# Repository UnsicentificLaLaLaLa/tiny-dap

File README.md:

# tiny-dap

[TOC]

## 介绍

基于 TinyUSB 和 CMSIS-5 实现的 CMSIS-DAP，支持 SWD 调试接口和串口通信。

选择 TinyUSB 作为协议栈的原因是 TinyUSB 开源免费，且适配多家 MCU，具有良好的通用性。

基于 CMSIS-5 实现 CMSIS-DAP 可以降低移植 DapLink 的难度，降低实现门槛。

## 文件结构

- hardware

    - v1.x

        tiny-dap 的硬件实现，使用 KiCad 7.0 设计，已生成生产文件和原理图。

        - production

            使用 KiCad 嘉立创提供的插件生成的生产文件。

- software

    tiny-dap 的软件实现，基于 MM32F0162D4Q。

## 适配芯片

目前计划采用 MM32F0162D4Q 作为 tiny-dap 的 MCU，后续也将计划在更多 QFN32 芯片上实现 tiny-dap，如果有精力的话。

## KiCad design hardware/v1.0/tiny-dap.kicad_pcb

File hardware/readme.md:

- v1.0
    - 初版 tiny-dap 硬件，基于 MM32F0162D4Q 设计
- v1.1
    - 基于 v1.0，移除了复位电路，移除了一个 LED，移除了微控制器电源的电容，移除了 USB 信号线上串联的 22R 电阻，减小了 PCB 尺寸

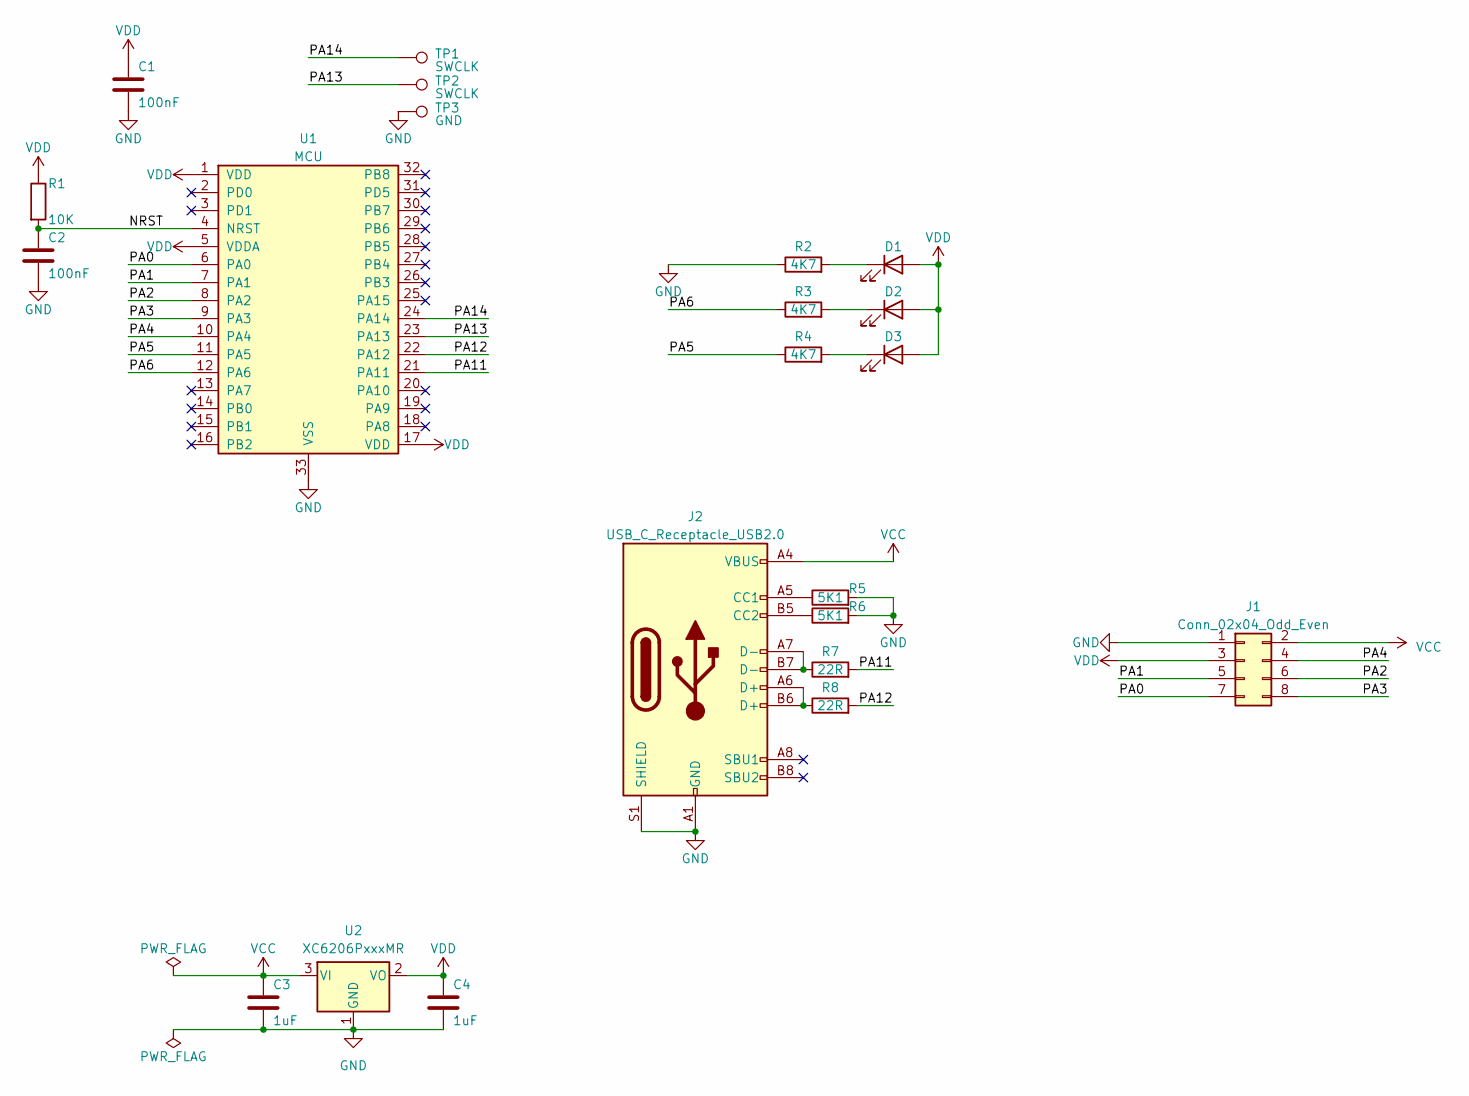
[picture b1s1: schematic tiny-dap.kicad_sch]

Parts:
C1, C2: 100nF; C_0603_1608Metric_Pad1.08x0.95mm_HandSolder
C3, C4: 1uF; C_0603_1608Metric_Pad1.08x0.95mm_HandSolder
D1, D2, D3: LED; LED_0603_1608Metric_Pad1.05x0.95mm_HandSolder
J1: Conn_02x04_Odd_Even; PinHeader_2x04_P2.54mm_Horizonal_Edge
J2: USB_C_Receptacle_USB2.0; USB_C_Receptacle_HRO_TYPE-C-31-M-12
R1: 10K; R_0603_1608Metric_Pad0.98x0.95mm_HandSolder
R2, R3, R4: 4K7; R_0603_1608Metric_Pad0.98x0.95mm_HandSolder
R5, R6: 5K1; R_0603_1608Metric_Pad0.98x0.95mm_HandSolder
R7, R8: 22R; R_0603_1608Metric_Pad0.98x0.95mm_HandSolder
TP1, TP2: SWCLK; TestPoint_Pad_D1.0mm
TP3: GND; TestPoint_Pad_D1.0mm
U1: MCU; QFN-32-1EP_5x5mm_P0.5mm_EP3.6x3.6mm
U2: XC6206PxxxMR; SOT-23

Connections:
/NRST: C2.1, R1.2, U1.4 (NRST)
/PA0: J1.7, U1.6 (PA0)
/PA1: J1.5, U1.7 (PA1)
/PA2: J1.6, U1.8 (PA2)
/PA3: J1.8, U1.9 (PA3)
/PA4: J1.4, U1.10 (PA4)
/PA5: R4.1, U1.11 (PA5)
/PA6: R3.1, U1.12 (PA6)
/PA11: R7.2, U1.21 (PA11)
/PA12: R8.2, U1.22 (PA12)
/PA13: TP2.1, U1.23 (PA13)
/PA14: TP1.1, U1.24 (PA14)
GND: C1.2, C2.2, C3.2, C4.2, J1.1, J2.A1 (GND), J2.A12 (GND), J2.B1 (GND), J2.B12 (GND), J2.S1 (SHIELD), R2.1, R5.2, R6.2, TP3.1, U1.33 (VSS), U2.1 (GND)
unnamed: D1.1 (K), R2.2
unnamed: D2.1 (K), R3.2
unnamed: D3.1 (K), R4.2
unnamed: J2.A5 (CC1), R5.1
unnamed: J2.B5 (CC2), R6.1
unnamed: J2.A6 (D+), J2.B6 (D+), R8.1
unnamed: J2.A7 (D-), J2.B7 (D-), R7.1
VCC: C3.1, J1.2, J2.A4 (VBUS), J2.A9 (VBUS), J2.B4 (VBUS), J2.B9 (VBUS), U2.3 (VI)
VDD: C1.1, C4.1, D1.2 (A), D2.2 (A), D3.2 (A), J1.3, R1.1, U1.1 (VDD), U1.5 (VDDA), U1.17 (VDD), U2.2 (VO)

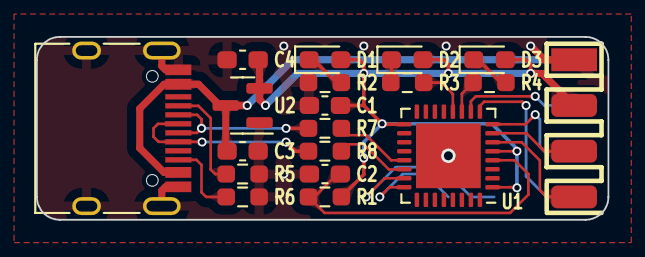
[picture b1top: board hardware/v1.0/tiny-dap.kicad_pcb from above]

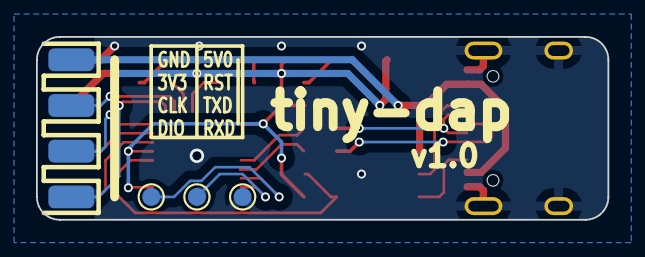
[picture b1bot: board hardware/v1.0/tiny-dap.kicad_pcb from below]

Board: 2 copper layers, 31.8 x 10.2 mm, 22 parts (3 on the bottom side), 22 nets.

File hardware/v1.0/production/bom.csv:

Designator,Footprint,Quantity,Value,LCSC Part #
"C1, C2",0603,2,100nF,
"C3, C4",0603,2,1uF,
"D1, D2, D3",0603,3,LED,
J1,PinHeader_2x04_P2.54mm_Horizonal_Edge,1,Conn_02x04_Odd_Even,
J2,USB_C_Receptacle_HRO_TYPE-C-31-M-12,1,USB_C_Receptacle_USB2.0,
R1,0603,1,10K,
"R2, R3, R4",0603,3,4K7,
"R5, R6",0603,2,5K1,
"R7, R8",0603,2,22R,
"TP1, TP2",TestPoint_Pad_D1.0mm,2,SWCLK,
TP3,TestPoint_Pad_D1.0mm,1,GND,
U1,QFN-32-1EP_5x5mm_P0.5mm_EP3.6x3.6mm,1,MCU,
U2,SOT-23,1,XC6206PxxxMR,

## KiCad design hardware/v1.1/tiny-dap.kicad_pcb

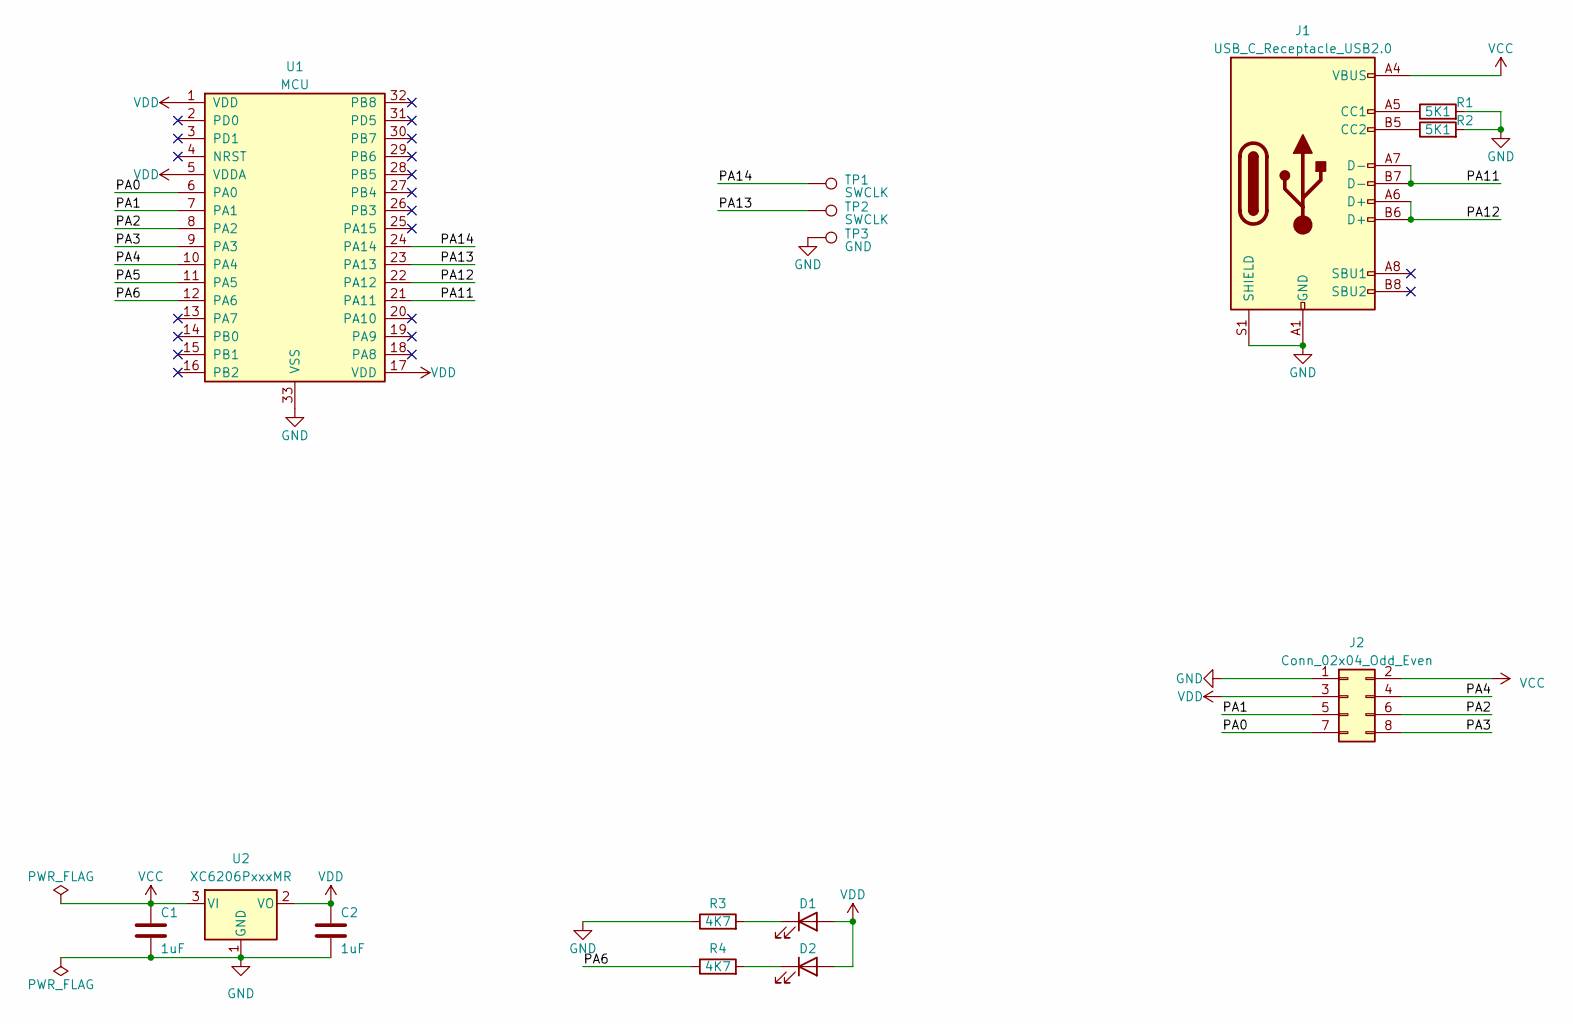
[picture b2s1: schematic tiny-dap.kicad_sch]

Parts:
C1, C2: 1uF; C_0603_1608Metric_Pad1.08x0.95mm_HandSolder
D1, D2: LED; LED_0603_1608Metric_Pad1.05x0.95mm_HandSolder
J1: USB_C_Receptacle_USB2.0; USB_C_Receptacle_HRO_TYPE-C-31-M-12
J2: Conn_02x04_Odd_Even; PinHeader_2x04_P2.54mm_Horizonal_Edge
R1, R2: 5K1; R_0603_1608Metric_Pad0.98x0.95mm_HandSolder
R3, R4: 4K7; R_0603_1608Metric_Pad0.98x0.95mm_HandSolder
TP1, TP2: SWCLK; TestPoint_Pad_D1.0mm
TP3: GND; TestPoint_Pad_D1.0mm
U1: MCU; QFN-32-1EP_5x5mm_P0.5mm_EP3.6x3.6mm
U2: XC6206PxxxMR; SOT-23

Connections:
/PA0: J2.7, U1.6 (PA0)
/PA1: J2.5, U1.7 (PA1)
/PA2: J2.6, U1.8 (PA2)
/PA3: J2.8, U1.9 (PA3)
/PA4: J2.4, U1.10 (PA4)
/PA5: U1.11 (PA5)
/PA6: R4.1, U1.12 (PA6)
/PA11: J1.A7 (D-), J1.B7 (D-), U1.21 (PA11)
/PA12: J1.A6 (D+), J1.B6 (D+), U1.22 (PA12)
/PA13: TP2.1, U1.23 (PA13)
/PA14: TP1.1, U1.24 (PA14)
GND: C1.2, C2.2, J1.A1 (GND), J1.A12 (GND), J1.B1 (GND), J1.B12 (GND), J1.S1 (SHIELD), J2.1, R1.2, R2.2, R3.1, TP3.1, U1.33 (VSS), U2.1 (GND)
unnamed: D1.1 (K), R3.2
unnamed: D2.1 (K), R4.2
unnamed: J1.A5 (CC1), R1.1
unnamed: J1.B5 (CC2), R2.1
VCC: C1.1, J1.A4 (VBUS), J1.A9 (VBUS), J1.B4 (VBUS), J1.B9 (VBUS), J2.2, U2.3 (VI)
VDD: C2.1, D1.2 (A), D2.2 (A), J2.3, U1.1 (VDD), U1.5 (VDDA), U1.17 (VDD), U2.2 (VO)

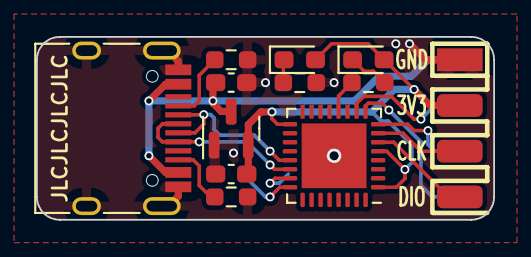
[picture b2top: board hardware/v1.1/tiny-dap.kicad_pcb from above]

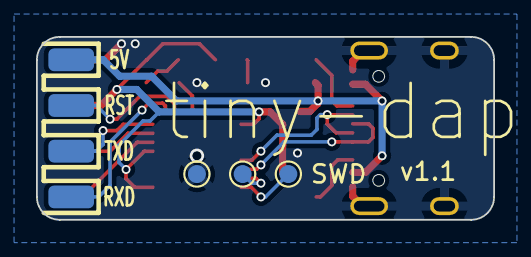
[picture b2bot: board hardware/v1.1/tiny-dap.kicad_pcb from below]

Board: 2 copper layers, 25.4 x 10.2 mm, 15 parts (3 on the bottom side), 17 nets.

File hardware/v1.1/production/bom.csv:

Designator,Footprint,Quantity,Value,LCSC Part #
"C1, C2",0603,2,1uF,
"D1, D2",0603,2,LED,
J1,USB_C_Receptacle_HRO_TYPE-C-31-M-12,1,USB_C_Receptacle_USB2.0,
J2,PinHeader_2x04_P2.54mm_Horizonal_Edge,1,Conn_02x04_Odd_Even,
"R1, R2",0603,2,5K1,
"R3, R4",0603,2,4K7,
"TP1, TP2",TestPoint_Pad_D1.0mm,2,SWCLK,
TP3,TestPoint_Pad_D1.0mm,1,GND,
U1,QFN-32-1EP_5x5mm_P0.5mm_EP3.6x3.6mm,1,MCU,
U2,SOT-23,1,XC6206PxxxMR,

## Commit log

2023-08-16 add hardware v1.0.
    - add tiny-dap 1.0 pcb design file.
2023-08-16 add hardware v1.1.
    - add tiny-dap v1.1 pcb file.
2023-08-16 update readme.
    - update readme file, add tiny-dap intro.
2023-08-16 add tiny-dap software.
    - add source code.
2023-08-16 hardware bugfix.
    - modify usb cc pin res val 22R -> 5K1.
